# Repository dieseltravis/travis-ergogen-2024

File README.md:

# Travis's Ergogen Keyboard 2024 #
Built with Ergogen v4. *Beta* quality!

## Project Details ##
* `/config.yaml` Ergogen layout
* `/package.json` yarn commands and metadata
* `/output/outlines/` generated 2d models
* `/output/cases/` generated 3d models
* `/output/pcbs/` generated PCB
* `/footprints/travis/` Custom parts' footprints
    * `/footprints/travis/travis.pretty/` KiCad footprints
* `/key/` generator for individual key footprint (key-module.js)
    * `/keytest/` test for individual key footprint
* `/datasheets/` PDFs for some of the parts used
* `/kle/` keyboard-layout-editor.com layouts
* `/firmware/` qmk firmware compiles, but needs to be tested!

## References ##
* Ergogen project: https://github.com/ergogen/ergogen/
    * https://ergogen.cache.works/
    * https://ergogen.xyz/
* FlatFootFox's Let's Design A Keyboard With Ergogen v4 https://flatfootfox.com/ergogen-introduction/
* Footprints:
    * ceoloide's Ergogen PCB footprints https://github.com/ceoloide/ergogen-footprints
    * infused-kim's Ergogen PCB footprints https://github.com/infused-kim/kb_ergogen_fp/
    * TildeWill's Ergogen PCB footprints https://github.com/TildeWill/ergogen_footprints
    * MvEerd https://github.com/MvEerd/ergogen/tree/mveerd/src/footprints
    * daprice's keyswitches.pretty https://github.com/daprice/keyswitches.pretty
    * joe-scotto's scottokeebs: https://github.com/joe-scotto/scottokeebs/tree/main/Extras/ScottoKicad
    * Convert Kicad Footprints to Ergogen https://nilnil.notion.site/Convert-Kicad-Footprints-to-Ergogen-8340ce87ad554c69af4e3f92bc9a0898
    * KiCad Footprints: https://kicad.github.io/footprints/
* Other helpful build guides:
    * ceoloide's corney-island build https://github.com/ceoloide/corney-island
    * zzeneg's stront40 https://github.com/zzeneg/stront/tree/stront40
    * Minecatr's Splinar+ https://github.com/Minecatr/keyboards/
    * Kimiko Build Guide https://keycapsss.com/help/kimiko/buildguide_en
    * Nullbits Nibble https://github.com/nullbitsco/docs/blob/main/nibble/build_guide_en.md
    * Lagom https://github.com/mohoyt/lagom/
    * Sundown-keyboard https://github.com/Richiban/Sundown-keyboard/
    * Mantis hex ergo keyboard https://github.com/fxkuehl/mantis/
    * Sofle Keyboard https://github.com/josefadamcik/SofleKeyboard

## Parts ##

Aliexpress:
* Diodes: DO-35 1N4148 100pcs https://www.aliexpress.us/item/3256805608834808.html
* Rotary encoder: EC11 12.5mm 5pcs https://www.aliexpress.us/item/2251832789732148.html
* EVQWGD001 Encoder: https://www.aliexpress.us/item/3256806010310254.html
* IC SN74HC138N 10pcs https://www.aliexpress.us/item/3256806021872320.html
* RGB LEDs: SK6812 MINI-E 100pcs https://www.aliexpress.us/item/2255800289371100.html
* Capacitors: 104(0.1uF) 100pcs https://www.aliexpress.us/item/3256802104127109.html
* Resistor: 470R 100pcs https://www.aliexpress.us/item/3256801441680644.html
* Electrolytic Capacitor: 6.3V1000UF 6x11mm 10pcs https://www.aliexpress.us/item/3256802796040934.html

Adafruit:
* Adafruit KB2040 - RP2040 Kee Boar Driver https://www.adafruit.com/product/5302
* 5 @ Kailh Switch Sockets for MX-compatible Mechanical Keys - 20 Pack https://www.adafruit.com/product/4958
* 10 @ Kailh Mechanical Key Switches - Tactile Brown - 10 pack - Cherry MX Brown Compatible https://www.adafruit.com/product/4954
* 10 @ DSA Keycaps for MX Compatible Switches - 10 pack https://www.adafruit.com/product/5008
* USB A to USB C Cable - 2 meters long https://www.adafruit.com/product/5044

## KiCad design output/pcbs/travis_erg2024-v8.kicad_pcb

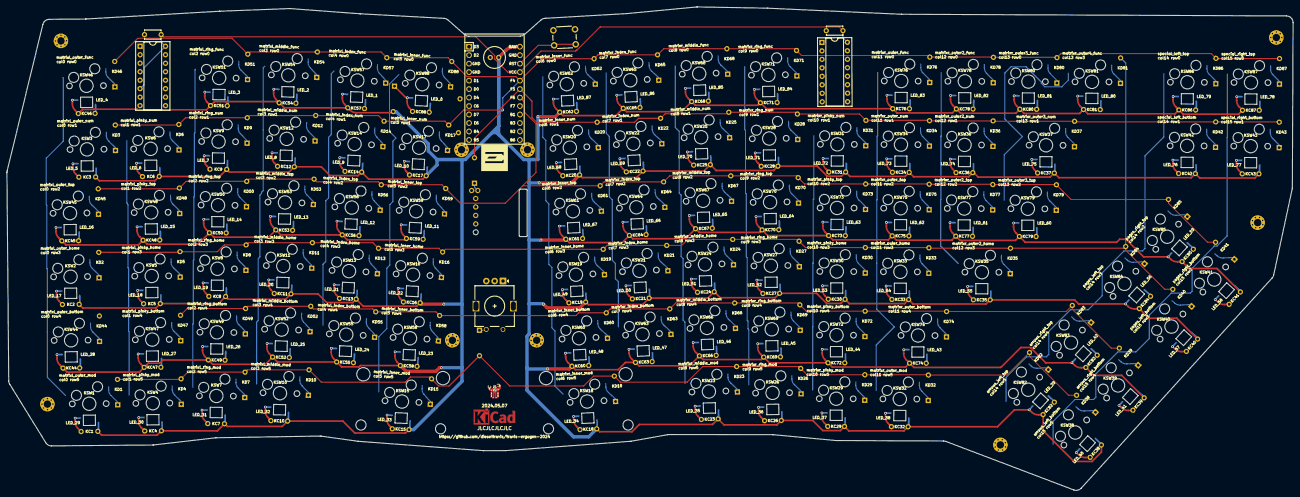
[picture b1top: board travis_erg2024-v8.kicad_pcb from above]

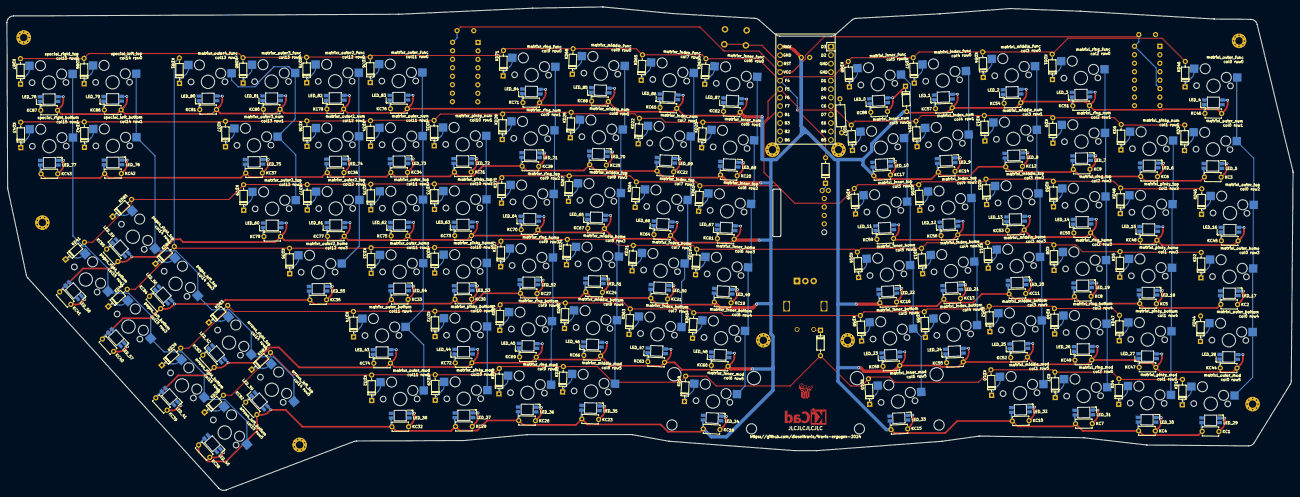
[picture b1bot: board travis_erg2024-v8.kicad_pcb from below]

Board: 2 copper layers, 385.3 x 144.8 mm, 379 parts (268 on the bottom side), 214 nets.

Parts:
C1: 6.3V 1000uF; C_Radial_D6.3mm_H11.0mm_P2.50mm
C2, C3: 104; C_Disc_D4.7mm_W2.5mm_P5.00mm
D1, D2, D3: 1N4148; Diode_DO-35
DIP1, DIP2: SN74HC138N; DIP-16_W7.62mm_Socket
HOLE1, HOLE2, HOLE3, HOLE4, HOLE5, HOLE6, HOLE7, HOLE8, HOLE9: MountingHole_2.2mm_M2_Pad_Via
KC1, KC2, KC3, KC4, KC5, KC6, KC7, KC8, KC9, KC10, KC11, KC12, KC13, KC14, KC15, KC16, KC17, KC18, KC19, KC20, KC21, KC22, KC23, KC24, KC25, KC26, KC27, KC28, KC29, KC30, KC31, KC32, KC33, KC34, KC35, KC36, KC37, KC38, KC39, KC40, KC41, KC42, KC43, KC44, KC45, KC46, KC47, KC48, KC49, KC50, KC51, KC52, KC53, KC54, KC55, KC56, KC57, KC58, KC59, KC60, KC61, KC62, KC63, KC64, KC65, KC66, KC67, KC68, KC69, KC70, KC71, KC72, KC73, KC74, KC75, KC76, KC77, KC78, KC79, KC80, KC81, KC82, KC83, KC84, KC85, KC86, KC87, KC88: 104; C_Disc_D4.7mm_W2.5mm_P5.00mm
KD1, KD2, KD3, KD4, KD5, KD6, KD7, KD8, KD9, KD10, KD11, KD12, KD13, KD14, KD15, KD16, KD17, KD18, KD19, KD20, KD21, KD22, KD23, KD24, KD25, KD26, KD27, KD28, KD29, KD30, KD31, KD32, KD33, KD34, KD35, KD36, KD37, KD38, KD39, KD40, KD41, KD42, KD43, KD44, KD45, KD46, KD47, KD48, KD49, KD50, KD51, KD52, KD53, KD54, KD55, KD56, KD57, KD58, KD59, KD60, KD61, KD62, KD63, KD64, KD65, KD66, KD67, KD68, KD69, KD70, KD71, KD72, KD73, KD74, KD75, KD76, KD77, KD78, KD79, KD80, KD81, KD82, KD83, KD84, KD85, KD86, KD87, KD88: 1N4148; Diode_DO-35
KSW1, KSW2, KSW3, KSW4, KSW5, KSW6, KSW7, KSW8, KSW9, KSW10, KSW11, KSW12, KSW13, KSW14, KSW15, KSW16, KSW17, KSW18, KSW19, KSW20, KSW21, KSW22, KSW23, KSW24, KSW25, KSW26, KSW27, KSW28, KSW29, KSW30, KSW31, KSW32, KSW33, KSW34, KSW35, KSW36, KSW37, KSW38, KSW39, KSW40, KSW41, KSW42, KSW43, KSW44, KSW45, KSW46, KSW47, KSW48, KSW49, KSW50, KSW51, KSW52, KSW53, KSW54, KSW55, KSW56, KSW57, KSW58, KSW59, KSW60, KSW61, KSW62, KSW63, KSW64, KSW65, KSW66, KSW67, KSW68, KSW69, KSW70, KSW71, KSW72, KSW73, KSW74, KSW75, KSW76, KSW77, KSW78, KSW79, KSW80, KSW81, KSW82, KSW83, KSW84, KSW85, KSW86, KSW87, KSW88: Kailh MX Switch Sockets; MX
LED_0-row0-col5, LED_1-row0-col4, LED_2-row0-col3, LED_3-row0-col2, LED_4-row0-col0, LED_5-row1-col0, LED_6-row1-col1, LED_7-row1-col2, LED_8-row1-col3, LED_9-row1-col4, LED_10-row1-col5, LED_11-row2-col5, LED_12-row2-col4, LED_13-row2-col3, LED_14-row2-col2, LED_15-row2-col1, LED_16-row2-col0, LED_17-row3-col0, LED_18-row3-col1, LED_19-row3-col2, LED_20-row3-col3, LED_21-row3-col4, LED_22-row3-col5, LED_23-row4-col5, LED_24-row4-col4, LED_25-row4-col3, LED_26-row4-col2, LED_27-row4-col1, LED_28-row4-col0, LED_29-row5-col0, LED_30-row5-col1, LED_31-row5-col2, LED_32-row5-col3, LED_33-row5-col5, LED_34-row5-col6, LED_35-row5-col8, LED_36-row5-col9, LED_37-row5-col10, LED_38-row5-col11, LED_39-row5-col14, LED_40-row5-col15, LED_41-row4-col15, LED_42-row4-col14, LED_43-row4-col11, LED_44-row4-col10, LED_45-row4-col9, LED_46-row4-col8, LED_47-row4-col7, LED_48-row4-col6, LED_49-row3-col6, LED_50-row3-col7, LED_51-row3-col8, LED_52-row3-col9, LED_53-row3-col10, LED_54-row3-col11, LED_55-row3-col12, LED_56-row3-col14, LED_57-row3-col15, LED_58-row2-col15, LED_59-row2-col14, LED_60-row2-col13, LED_61-row2-col12, LED_62-row2-col11, LED_63-row2-col10, LED_64-row2-col9, LED_65-row2-col8, LED_66-row2-col7, LED_67-row2-col6, LED_68-row1-col6, LED_69-row1-col7, LED_70-row1-col8, LED_71-row1-col9, LED_72-row1-col10, LED_73-row1-col11, LED_74-row1-col12, LED_75-row1-col13, LED_76-row1-col14, LED_77-row1-col15, LED_78-row0-col15, LED_79-row0-col14, LED_80-row3-col13, LED_81-row0-col13, LED_82-row0-col12, LED_83-row0-col11, LED_84-row0-col9, LED_85-row0-col8, LED_86-row0-col7, LED_87-row0-col6: SK6812mini-e; led_SK6812mini-e
LOGO1: ergogen_logo
LOGO2: travis
MCU1: Arduino Pro Micro; Arduino_Pro_Micro
R1: 470R; R_Axial_DIN0207_L6.3mm_D2.5mm_P10.16mm_Horizontal
ROT1: EC11; ec11
SCR1: EVQWGD001; evqwgd001
STAB2u1, STAB2u2: Stabilizer_MX_2.00u
SW1: 6mm button; SW_PUSH_6mm_H4.3mm
SYM1: KiCad-Logo_5mm_Copper

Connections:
GND: C1.2, C2.2, C3.2, DIP1.4, DIP1.8, DIP2.4, DIP2.5, DIP2.8, KC1.2, KC2.2, KC3.2, KC4.2, KC5.2, KC6.2, KC7.2, KC8.2, KC9.2, KC10.2, KC11.2, KC12.2, KC13.2, KC14.2, KC15.2, KC16.2, KC17.2, KC18.2, KC19.2, KC20.2, KC21.2, KC22.2, KC23.2, KC24.2, KC25.2, KC26.2, KC27.2, KC28.2, KC29.2, KC30.2, KC31.2, KC32.2, KC33.2, KC34.2, KC35.2, KC36.2, KC37.2, KC38.2, KC39.2, KC40.2, KC41.2, KC42.2, KC43.2, KC44.2, KC45.2, KC46.2, KC47.2, KC48.2, KC49.2, KC50.2, KC51.2, KC52.2, KC53.2, KC54.2, KC55.2, KC56.2, KC57.2, KC58.2, KC59.2, KC60.2, KC61.2, KC62.2, KC63.2, KC64.2, KC65.2, KC66.2, KC67.2, KC68.2, KC69.2, KC70.2, KC71.2, KC72.2, KC73.2, KC74.2, KC75.2, KC76.2, KC77.2, KC78.2, KC79.2, KC80.2, KC81.2, KC82.2, KC83.2, KC84.2, KC85.2, KC86.2, KC87.2, KC88.2, LED_0-row0-col5.3, LED_1-row0-col4.3, LED_2-row0-col3.3, LED_3-row0-col2.3, LED_4-row0-col0.3, LED_5-row1-col0.3, LED_6-row1-col1.3, LED_7-row1-col2.3, LED_8-row1-col3.3, LED_9-row1-col4.3, LED_10-row1-col5.3, LED_11-row2-col5.3, LED_12-row2-col4.3, LED_13-row2-col3.3, LED_14-row2-col2.3, LED_15-row2-col1.3, LED_16-row2-col0.3, LED_17-row3-col0.3, LED_18-row3-col1.3, LED_19-row3-col2.3, LED_20-row3-col3.3, LED_21-row3-col4.3, LED_22-row3-col5.3, LED_23-row4-col5.3, LED_24-row4-col4.3, LED_25-row4-col3.3, LED_26-row4-col2.3, LED_27-row4-col1.3, LED_28-row4-col0.3, LED_29-row5-col0.3, LED_30-row5-col1.3, LED_31-row5-col2.3, LED_32-row5-col3.3, LED_33-row5-col5.3, LED_34-row5-col6.3, LED_35-row5-col8.3, LED_36-row5-col9.3, LED_37-row5-col10.3, LED_38-row5-col11.3, LED_39-row5-col14.3, LED_40-row5-col15.3, LED_41-row4-col15.3, LED_42-row4-col14.3, LED_43-row4-col11.3, LED_44-row4-col10.3, LED_45-row4-col9.3, LED_46-row4-col8.3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
LED: MCU1.12, R1.1
LED_0: LED_0-row0-col5.4, R1.2
LED_1: LED_0-row0-col5.2, LED_1-row0-col4.4
LED_2: LED_1-row0-col4.2, LED_2-row0-col3.4
LED_3: LED_2-row0-col3.2, LED_3-row0-col2.4
LED_4: LED_3-row0-col2.2, LED_4-row0-col0.4
LED_5: LED_4-row0-col0.2, LED_5-row1-col0.4
LED_6: LED_5-row1-col0.2, LED_6-row1-col1.4
LED_7: LED_6-row1-col1.2, LED_7-row1-col2.4
LED_8: LED_7-row1-col2.2, LED_8-row1-col3.4
LED_9: LED_8-row1-col3.2, LED_9-row1-col4.4
LED_10: LED_9-row1-col4.2, LED_10-row1-col5.4
LED_11: LED_10-row1-col5.2, LED_11-row2-col5.4
LED_12: LED_11-row2-col5.2, LED_12-row2-col4.4
LED_13: LED_12-row2-col4.2, LED_13-row2-col3.4
LED_14: LED_13-row2-col3.2, LED_14-row2-col2.4
LED_15: LED_14-row2-col2.2, LED_15-row2-col1.4
LED_16: LED_15-row2-col1.2, LED_16-row2-col0.4
LED_17: LED_16-row2-col0.2, LED_17-row3-col0.4
LED_18: LED_17-row3-col0.2, LED_18-row3-col1.4
LED_19: LED_18-row3-col1.2, LED_19-row3-col2.4
LED_20: LED_19-row3-col2.2, LED_20-row3-col3.4
LED_21: LED_20-row3-col3.2, LED_21-row3-col4.4
LED_22: LED_21-row3-col4.2, LED_22-row3-col5.4
LED_23: LED_22-row3-col5.2, LED_23-row4-col5.4
LED_24: LED_23-row4-col5.2, LED_24-row4-col4.4
LED_25: LED_24-row4-col4.2, LED_25-row4-col3.4
LED_26: LED_25-row4-col3.2, LED_26-row4-col2.4
LED_27: LED_26-row4-col2.2, LED_27-row4-col1.4
LED_28: LED_27-row4-col1.2, LED_28-row4-col0.4
LED_29: LED_28-row4-col0.2, LED_29-row5-col0.4
LED_30: LED_29-row5-col0.2, LED_30-row5-col1.4
LED_31: LED_30-row5-col1.2, LED_31-row5-col2.4
LED_32: LED_31-row5-col2.2, LED_32-row5-col3.4
LED_33: LED_32-row5-col3.2, LED_33-row5-col5.4
LED_34: LED_33-row5-col5.2, LED_34-row5-col6.4
LED_35: LED_34-row5-col6.2, LED_35-row5-col8.4
LED_36: LED_35-row5-col8.2, LED_36-row5-col9.4
LED_37: LED_36-row5-col9.2, LED_37-row5-col10.4
LED_38: LED_37-row5-col10.2, LED_38-row5-col11.4
LED_39: LED_38-row5-col11.2, LED_39-row5-col14.4
LED_40: LED_39-row5-col14.2, LED_40-row5-col15.4
LED_41: LED_40-row5-col15.2, LED_41-row4-col15.4
LED_42: LED_41-row4-col15.2, LED_42-row4-col14.4
LED_43: LED_42-row4-col14.2, LED_43-row4-col11.4
LED_44: LED_43-row4-col11.2, LED_44-row4-col10.4
LED_45: LED_44-row4-col10.2, LED_45-row4-col9.4
LED_46: LED_45-row4-col9.2, LED_46-row4-col8.4
LED_47: LED_46-row4-col8.2, LED_47-row4-col7.4
LED_48: LED_47-row4-col7.2, LED_48-row4-col6.4
LED_49: LED_48-row4-col6.2, LED_49-row3-col6.4
LED_50: LED_49-row3-col6.2, LED_50-row3-col7.4
LED_51: LED_50-row3-col7.2, LED_51-row3-col8.4
LED_52: LED_51-row3-col8.2, LED_52-row3-col9.4
LED_53: LED_52-row3-col9.2, LED_53-row3-col10.4
LED_54: LED_53-row3-col10.2, LED_54-row3-col11.4
LED_55: LED_54-row3-col11.2, LED_55-row3-col12.4
LED_56: LED_55-row3-col12.2, LED_56-row3-col14.4
LED_57: LED_56-row3-col14.2, LED_57-row3-col15.4
LED_58: LED_57-row3-col15.2, LED_58-row2-col15.4
LED_59: LED_58-row2-col15.2, LED_59-row2-col14.4
LED_60: LED_59-row2-col14.2, LED_60-row2-col13.4
LED_61: LED_60-row2-col13.2, LED_61-row2-col12.4
LED_62: LED_61-row2-col12.2, LED_62-row2-col11.4
LED_63: LED_62-row2-col11.2, LED_63-row2-col10.4
LED_64: LED_63-row2-col10.2, LED_64-row2-col9.4
LED_65: LED_64-row2-col9.2, LED_65-row2-col8.4
LED_66: LED_65-row2-col8.2, LED_66-row2-col7.4
LED_67: LED_66-row2-col7.2, LED_67-row2-col6.4
LED_68: LED_67-row2-col6.2, LED_68-row1-col6.4
LED_69: LED_68-row1-col6.2, LED_69-row1-col7.4
LED_70: LED_69-row1-col7.2, LED_70-row1-col8.4
LED_71: LED_70-row1-col8.2, LED_71-row1-col9.4
LED_72: LED_71-row1-col9.2, LED_72-row1-col10.4
LED_73: LED_72-row1-col10.2, LED_73-row1-col11.4
LED_74: LED_73-row1-col11.2, LED_74-row1-col12.4
LED_75: LED_74-row1-col12.2, LED_75-row1-col13.4
LED_76: LED_75-row1-col13.2, LED_76-row1-col14.4
LED_77: LED_76-row1-col14.2, LED_77-row1-col15.4
LED_78: LED_77-row1-col15.2, LED_78-row0-col15.4
LED_79: LED_78-row0-col15.2, LED_79-row0-col14.4
LED_80: LED_79-row0-col14.2, LED_80-row3-col13.4
LED_81: LED_80-row3-col13.2, LED_81-row0-col13.4
LED_82: LED_81-row0-col13.2, LED_82-row0-col12.4
LED_83: LED_82-row0-col12.2, LED_83-row0-col11.4
LED_84: LED_83-row0-col11.2, LED_84-row0-col9.4
LED_85: LED_84-row0-col9.2, LED_85-row0-col8.4
LED_86: LED_85-row0-col8.2, LED_86-row0-col7.4
LED_87: LED_86-row0-col7.2, LED_87-row0-col6.4
RAW: C1.1, D1.2, KC1.1, KC2.1, KC3.1, KC4.1, KC5.1, KC6.1, KC7.1, KC8.1, KC9.1, KC10.1, KC11.1, KC12.1, KC13.1, KC14.1, KC15.1, KC16.1, KC17.1, KC18.1, KC19.1, KC20.1, KC21.1, KC22.1, KC23.1, KC24.1, KC25.1, KC26.1, KC27.1, KC28.1, KC29.1, KC30.1, KC31.1, KC32.1, KC33.1, KC34.1, KC35.1, KC36.1, KC37.1, KC38.1, KC39.1, KC40.1, KC41.1, KC42.1, KC43.1, KC44.1, KC45.1, KC46.1, KC47.1, KC48.1, KC49.1, KC50.1, KC51.1, KC52.1, KC53.1, KC54.1, KC55.1, KC56.1, KC57.1, KC58.1, KC59.1, KC60.1, KC61.1, KC62.1, KC63.1, KC64.1, KC65.1, KC66.1, KC67.1, KC68.1, KC69.1, KC70.1, KC71.1, KC72.1, KC73.1, KC74.1, KC75.1, KC76.1, KC77.1, KC78.1, KC79.1, KC80.1, KC81.1, KC82.1, KC83.1, KC84.1, KC85.1, KC86.1, KC87.1, LED_1-row0-col4.1, LED_2-row0-col3.1, LED_3-row0-col2.1, LED_4-row0-col0.1, LED_5-row1-col0.1, LED_6-row1-col1.1, LED_7-row1-col2.1, LED_8-row1-col3.1, LED_9-row1-col4.1, LED_10-row1-col5.1, LED_11-row2-col5.1, LED_12-row2-col4.1, LED_13-row2-col3.1, LED_14-row2-col2.1, LED_15-row2-col1.1, LED_16-row2-col0.1, LED_17-row3-col0.1, LED_18-row3-col1.1, LED_19-row3-col2.1, LED_20-row3-col3.1, LED_21-row3-col4.1, LED_22-row3-col5.1, LED_23-row4-col5.1, LED_24-row4-col4.1, LED_25-row4-col3.1, LED_26-row4-col2.1, LED_27-row4-col1.1, LED_28-row4-col0.1, LED_29-row5-col0.1, LED_30-row5-col1.1, LED_31-row5-col2.1, LED_32-row5-col3.1, LED_33-row5-col5.1, LED_34-row5-col6.1, LED_35-row5-col8.1, LED_36-row5-col9.1, LED_37-row5-col10.1, LED_38-row5-col11.1, LED_39-row5-col14.1, LED_40-row5-col15.1, LED_41-row4-col15.1, LED_42-row4-col14.1, LED_43-row4-col11.1, LED_44-row4-col10.1, LED_45-row4-col9.1, LED_46-row4-col8.1, LED_47-row4-col7.1, LED_48-row4-col6.1, LED_49-row3-col6.1, LED_50-row3-col7.1, LED_51-row3-col8.1, LED_52-row3-col9.1, LED_53-row3-col10.1, LED_54-row3-col11.1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
RAWD: D1.1, KC88.1, LED_0-row0-col5.1
RST: MCU1.22, SW1.2
VCC: C2.1, C3.1, DIP1.6, DIP1.16, DIP2.16, MCU1.21
arrows_left_bottom: KD38.1, KSW38.2
arrows_left_top: KD82.1, KSW82.2
arrows_right_bottom: KD39.1, KSW39.2
arrows_right_top: KD83.1, KSW83.2
col0: DIP1.15, KSW1.1, KSW2.1, KSW3.1, KSW44.1, KSW45.1, KSW46.1
col1: DIP1.14, KSW4.1, KSW5.1, KSW6.1, KSW47.1, KSW48.1, SCR1.S1
col2: DIP1.13, KSW7.1, KSW8.1, KSW9.1, KSW49.1, KSW50.1, KSW51.1
col3: DIP1.12, KSW10.1, KSW11.1, KSW12.1, KSW52.1, KSW53.1, KSW54.1
col4: DIP1.11, KSW13.1, KSW14.1, KSW55.1, KSW56.1, KSW57.1, ROT1.1
col5: DIP1.10, KSW15.1, KSW16.1, KSW17.1, KSW58.1, KSW59.1, KSW88.1
col6: DIP1.9, KSW18.1, KSW19.1, KSW20.1, KSW60.1, KSW61.1, KSW62.1
col7: DIP1.7, KSW21.1, KSW22.1, KSW63.1, KSW64.1, KSW65.1
col8: DIP2.15, KSW23.1, KSW24.1, KSW25.1, KSW66.1, KSW67.1, KSW68.1
col9: DIP2.14, KSW26.1, KSW27.1, KSW28.1, KSW69.1, KSW70.1, KSW71.1
col10: DIP2.13, KSW29.1, KSW30.1, KSW31.1, KSW72.1, KSW73.1
col11: DIP2.12, KSW32.1, KSW33.1, KSW34.1, KSW74.1, KSW75.1, KSW76.1
col12: DIP2.11, KSW35.1, KSW36.1, KSW77.1, KSW78.1
col13: DIP2.10, KSW37.1, KSW79.1, KSW80.1, KSW81.1
col14: DIP2.9, KSW42.1, KSW82.1, KSW83.1, KSW84.1, KSW85.1, KSW86.1
col15: DIP2.7, KSW38.1, KSW39.1, KSW40.1, KSW41.1, KSW43.1, KSW87.1
encA: MCU1.14, ROT1.A
encC: MCU1.13, ROT1.C
enc_to: D3.1, ROT1.2
matrixl_index_bottom: KD55.1, KSW55.2
matrixl_index_func: KD57.1, KSW57.2
matrixl_index_home: KD13.1, KSW13.2
matrixl_index_num: KD14.1, KSW14.2
matrixl_index_top: KD56.1, KSW56.2
matrixl_inner_bottom: KD58.1, KSW58.2
matrixl_inner_func: KD88.1, KSW88.2
matrixl_inner_home: KD16.1, KSW16.2
matrixl_inner_mod: KD15.1, KSW15.2
matrixl_inner_num: KD17.1, KSW17.2
matrixl_inner_top: KD59.1, KSW59.2
matrixl_middle_bottom: KD52.1, KSW52.2
matrixl_middle_func: KD54.1, KSW54.2
matrixl_middle_home: KD11.1, KSW11.2
matrixl_middle_mod: KD10.1, KSW10.2
matrixl_middle_num: KD12.1, KSW12.2
matrixl_middle_top: KD53.1, KSW53.2
matrixl_outer_bottom: KD44.1, KSW44.2
matrixl_outer_func: KD46.1, KSW46.2
matrixl_outer_home: KD2.1, KSW2.2
matrixl_outer_mod: KD1.1, KSW1.2
matrixl_outer_num: KD3.1, KSW3.2
matrixl_outer_top: KD45.1, KSW45.2
matrixl_pinky_bottom: KD47.1, KSW47.2
matrixl_pinky_home: KD5.1, KSW5.2
matrixl_pinky_mod: KD4.1, KSW4.2
matrixl_pinky_num: KD6.1, KSW6.2
matrixl_pinky_top: KD48.1, KSW48.2
matrixl_ring_bottom: KD49.1, KSW49.2
matrixl_ring_func: KD51.1, KSW51.2
matrixl_ring_home: KD8.1, KSW8.2
matrixl_ring_mod: KD7.1, KSW7.2
matrixl_ring_num: KD9.1, KSW9.2
matrixl_ring_top: KD50.1, KSW50.2
matrixr_index_bottom: KD63.1, KSW63.2
matrixr_index_func: KD65.1, KSW65.2
matrixr_index_home: KD21.1, KSW21.2
matrixr_index_num: KD22.1, KSW22.2
matrixr_index_top: KD64.1, KSW64.2
matrixr_inner_bottom: KD60.1, KSW60.2
matrixr_inner_func: KD62.1, KSW62.2
matrixr_inner_home: KD19.1, KSW19.2
matrixr_inner_mod: KD18.1, KSW18.2
matrixr_inner_num: KD20.1, KSW20.2
matrixr_inner_top: KD61.1, KSW61.2
matrixr_middle_bottom: KD66.1, KSW66.2
matrixr_middle_func: KD68.1, KSW68.2
matrixr_middle_home: KD24.1, KSW24.2
matrixr_middle_mod: KD23.1, KSW23.2
matrixr_middle_num: KD25.1, KSW25.2
matrixr_middle_top: KD67.1, KSW67.2
matrixr_outer2_func: KD78.1, KSW78.2
matrixr_outer2_home: KD35.1, KSW35.2
matrixr_outer2_num: KD36.1, KSW36.2
matrixr_outer2_top: KD77.1, KSW77.2
matrixr_outer3_func: KD80.1, KSW80.2
matrixr_outer3_num: KD37.1, KSW37.2
matrixr_outer3_top: KD79.1, KSW79.2
matrixr_outer4_func: KD81.1, KSW81.2
matrixr_outer_bottom: KD74.1, KSW74.2
matrixr_outer_func: KD76.1, KSW76.2
matrixr_outer_home: KD33.1, KSW33.2
matrixr_outer_mod: KD32.1, KSW32.2
matrixr_outer_num: KD34.1, KSW34.2
matrixr_outer_top: KD75.1, KSW75.2
matrixr_pinky_bottom: KD72.1, KSW72.2
matrixr_pinky_home: KD30.1, KSW30.2
matrixr_pinky_mod: KD29.1, KSW29.2
matrixr_pinky_num: KD31.1, KSW31.2
matrixr_pinky_top: KD73.1, KSW73.2
matrixr_ring_bottom: KD69.1, KSW69.2
matrixr_ring_func: KD71.1, KSW71.2
matrixr_ring_home: KD27.1, KSW27.2
matrixr_ring_mod: KD26.1, KSW26.2
matrixr_ring_num: KD28.1, KSW28.2
matrixr_ring_top: KD70.1, KSW70.2
mux0: DIP1.1, DIP2.1, MCU1.8
mux1: DIP1.2, DIP2.2, MCU1.7
mux2: DIP1.3, DIP2.3, MCU1.6
mux3: DIP1.5, DIP2.6, MCU1.5
pages_left_bottom: KD40.1, KSW40.2
pages_left_top: KD84.1, KSW84.2
pages_right_bottom: KD41.1, KSW41.2
pages_right_top: KD85.1, KSW85.2
row0: D2.2, KD46.2, KD51.2, KD54.2, KD57.2, KD62.2, KD65.2, KD68.2, KD71.2, KD76.2, KD78.2, KD80.2, KD86.2, KD87.2, KD88.2, MCU1.20
row1: KD3.2, KD6.2, KD9.2, KD12.2, KD14.2, KD17.2, KD20.2, KD22.2, KD25.2, KD28.2, KD31.2, KD34.2, KD36.2, KD37.2, KD42.2, KD43.2, MCU1.19
row2: KD41.2, KD45.2, KD48.2, KD50.2, KD53.2, KD56.2, KD59.2, KD61.2, KD64.2, KD67.2, KD70.2, KD73.2, KD75.2, KD77.2, KD79.2, KD85.2, MCU1.18
row3: KD2.2, KD5.2, KD8.2, KD11.2, KD13.2, KD16.2, KD19.2, KD21.2, KD24.2, KD27.2, KD30.2, KD33.2, KD35.2, KD40.2, KD81.2, KD84.2, MCU1.17
row4: KD39.2, KD44.2, KD47.2, KD49.2, KD52.2, KD55.2, KD58.2, KD60.2, KD63.2, KD66.2, KD69.2, KD72.2, KD74.2, KD83.2, MCU1.16
row5: D3.2, KD1.2, KD4.2, KD7.2, KD10.2, KD15.2, KD18.2, KD23.2, KD26.2, KD29.2, KD32.2, KD38.2, KD82.2, MCU1.15
scrA: MCU1.10, SCR1.A
scrC: MCU1.9, SCR1.C
scr_to: D2.1, SCR1.S2
special_left_bottom: KD42.1, KSW42.2
special_left_top: KD86.1, KSW86.2
special_right_bottom: KD43.1, KSW43.2
special_right_top: KD87.1, KSW87.2

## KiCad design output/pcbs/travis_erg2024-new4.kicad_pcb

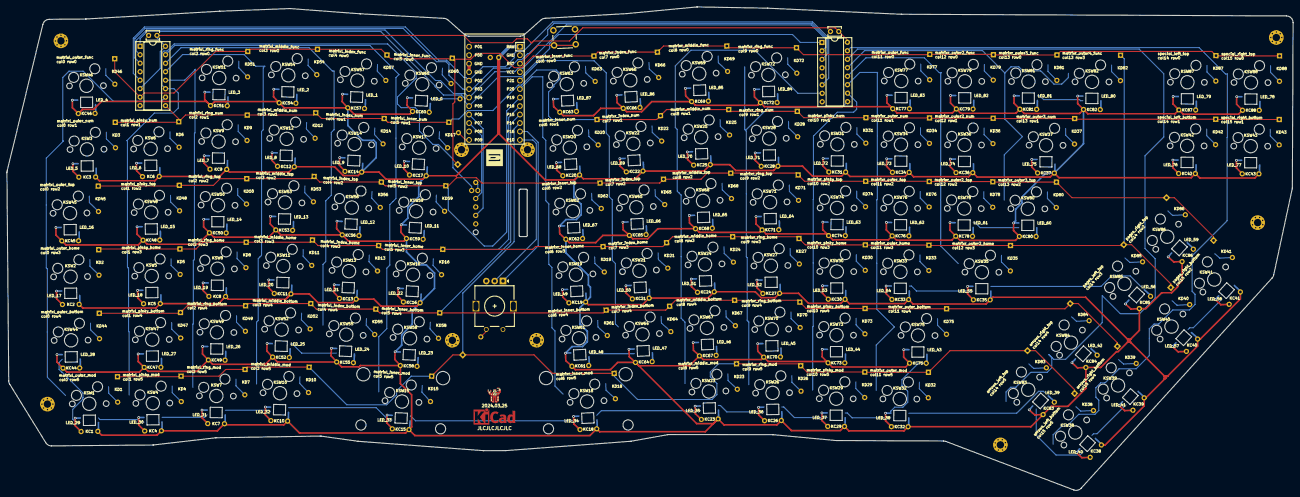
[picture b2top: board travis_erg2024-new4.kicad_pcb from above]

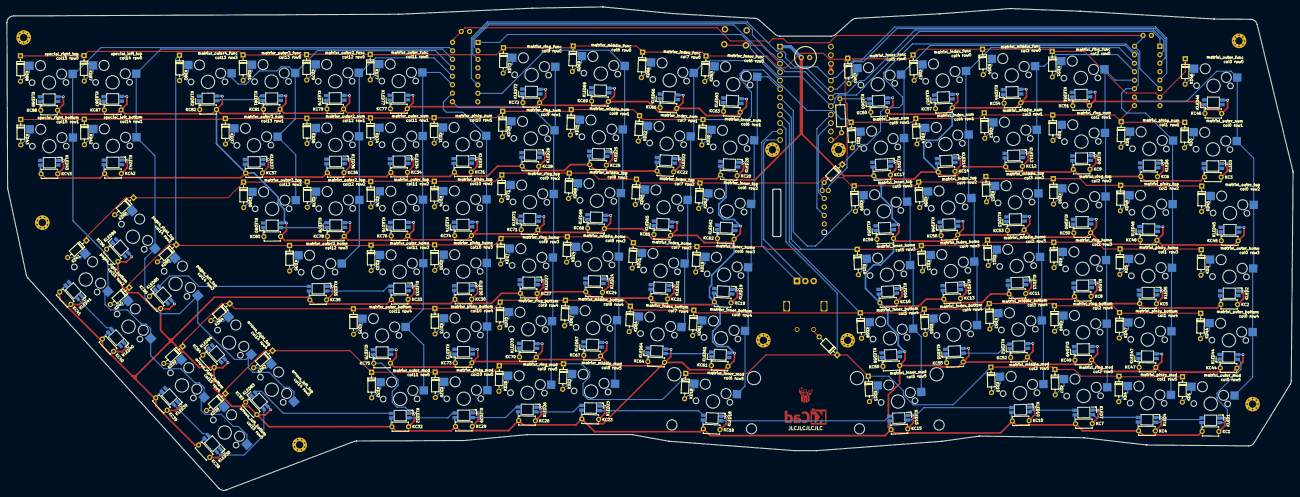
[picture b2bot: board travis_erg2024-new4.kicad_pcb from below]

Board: 2 copper layers, 385.3 x 144.8 mm, 377 parts (268 on the bottom side), 210 nets.

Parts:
C1: C_Radial_D6.3mm_H11.0mm_P2.50mm
C2, C3: C_Disc_D3.8mm_W2.6mm_P2.50mm
D1, D2: 1N4148; Diode_DO-35
DIP1, DIP2: DIP-16_W7.62mm_Socket
HOLE1, HOLE2, HOLE3, HOLE4, HOLE5, HOLE6, HOLE7, HOLE8, HOLE9: MountingHole_2.2mm_M2_Pad_Via
KC1, KC2, KC3, KC4, KC5, KC6, KC7, KC8, KC9, KC10, KC11, KC12, KC13, KC14, KC15, KC16, KC17, KC18, KC19, KC20, KC21, KC22, KC23, KC24, KC25, KC26, KC27, KC28, KC29, KC30, KC31, KC32, KC33, KC34, KC35, KC36, KC37, KC38, KC39, KC40, KC41, KC42, KC43, KC44, KC45, KC46, KC47, KC48, KC49, KC50, KC51, KC52, KC53, KC54, KC55, KC56, KC57, KC58, KC59, KC60, KC61, KC62, KC63, KC64, KC65, KC66, KC67, KC68, KC69, KC70, KC71, KC72, KC73, KC74, KC75, KC76, KC77, KC78, KC79, KC80, KC81, KC82, KC83, KC84, KC85, KC86, KC87, KC88: 104; C_Disc_D4.7mm_W2.5mm_P5.00mm
KD1, KD2, KD3, KD4, KD5, KD6, KD7, KD8, KD9, KD10, KD11, KD12, KD13, KD14, KD15, KD16, KD17, KD18, KD19, KD20, KD21, KD22, KD23, KD24, KD25, KD26, KD27, KD28, KD29, KD30, KD31, KD32, KD33, KD34, KD35, KD36, KD37, KD38, KD39, KD40, KD41, KD42, KD43, KD44, KD45, KD46, KD47, KD48, KD49, KD50, KD51, KD52, KD53, KD54, KD55, KD56, KD57, KD58, KD59, KD60, KD61, KD62, KD63, KD64, KD65, KD66, KD67, KD68, KD69, KD70, KD71, KD72, KD73, KD74, KD75, KD76, KD77, KD78, KD79, KD80, KD81, KD82, KD83, KD84, KD85, KD86, KD87, KD88: 1N4148; Diode_DO-35
KLED1, KLED2, KLED3, KLED4, KLED5, KLED6, KLED7, KLED8, KLED9, KLED10, KLED11, KLED12, KLED13, KLED14, KLED15, KLED16, KLED17, KLED18, KLED19, KLED20, KLED21, KLED22, KLED23, KLED24, KLED25, KLED26, KLED27, KLED28, KLED29, KLED30, KLED31, KLED32, KLED33, KLED34, KLED35, KLED36, KLED37, KLED38, KLED39, KLED40, KLED41, KLED42, KLED43, KLED44, KLED45, KLED46, KLED47, KLED48, KLED49, KLED50, KLED51, KLED52, KLED53, KLED54, KLED55, KLED56, KLED57, KLED58, KLED59, KLED60, KLED61, KLED62, KLED63, KLED64, KLED65, KLED66, KLED67, KLED68, KLED69, KLED70, KLED71, KLED72, KLED73, KLED74, KLED75, KLED76, KLED77, KLED78, KLED79, KLED80, KLED81, KLED82, KLED83, KLED84, KLED85, KLED86, KLED87, KLED88: SK6812mini-e; led_SK6812mini-e (per-key single-side)
KSW1, KSW2, KSW3, KSW4, KSW5, KSW6, KSW7, KSW8, KSW9, KSW10, KSW11, KSW12, KSW13, KSW14, KSW15, KSW16, KSW17, KSW18, KSW19, KSW20, KSW21, KSW22, KSW23, KSW24, KSW25, KSW26, KSW27, KSW28, KSW29, KSW30, KSW31, KSW32, KSW33, KSW34, KSW35, KSW36, KSW37, KSW38, KSW39, KSW40, KSW41, KSW42, KSW43, KSW44, KSW45, KSW46, KSW47, KSW48, KSW49, KSW50, KSW51, KSW52, KSW53, KSW54, KSW55, KSW56, KSW57, KSW58, KSW59, KSW60, KSW61, KSW62, KSW63, KSW64, KSW65, KSW66, KSW67, KSW68, KSW69, KSW70, KSW71, KSW72, KSW73, KSW74, KSW75, KSW76, KSW77, KSW78, KSW79, KSW80, KSW81, KSW82, KSW83, KSW84, KSW85, KSW86, KSW87, KSW88: Kailh MX Switch Sockets; MX
LOGO1: ergogen
LOGO2: travis
MCU1: ProMicro
R1: R_Axial_DIN0207_L6.3mm_D2.5mm_P10.16mm_Horizontal
ROT1: rotary_encoder
STAB2u1, STAB2u2: Stabilizer_MX_2.00u
SW1: SW_PUSH_6mm_H4.3mm
SYM1: KiCad-Logo_5mm_Copper

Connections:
GND: C1.2, C2.2, C3.2, DIP1.4, DIP1.8, DIP2.4, DIP2.5, DIP2.8, KC1.2, KC2.2, KC3.2, KC4.2, KC5.2, KC6.2, KC7.2, KC8.2, KC9.2, KC10.2, KC11.2, KC12.2, KC13.2, KC14.2, KC15.2, KC16.2, KC17.2, KC18.2, KC19.2, KC20.2, KC21.2, KC22.2, KC23.2, KC24.2, KC25.2, KC26.2, KC27.2, KC28.2, KC29.2, KC30.2, KC31.2, KC32.2, KC33.2, KC34.2, KC35.2, KC36.2, KC37.2, KC38.2, KC39.2, KC40.2, KC41.2, KC42.2, KC43.2, KC44.2, KC45.2, KC46.2, KC47.2, KC48.2, KC49.2, KC50.2, KC51.2, KC52.2, KC53.2, KC54.2, KC55.2, KC56.2, KC57.2, KC58.2, KC59.2, KC60.2, KC61.2, KC62.2, KC63.2, KC64.2, KC65.2, KC66.2, KC67.2, KC68.2, KC69.2, KC70.2, KC71.2, KC72.2, KC73.2, KC74.2, KC75.2, KC76.2, KC77.2, KC78.2, KC79.2, KC80.2, KC81.2, KC82.2, KC83.2, KC84.2, KC85.2, KC86.2, KC87.2, KC88.2, KLED1.3, KLED2.3, KLED3.3, KLED4.3, KLED5.3, KLED6.3, KLED7.3, KLED8.3, KLED9.3, KLED10.3, KLED11.3, KLED12.3, KLED13.3, KLED14.3, KLED15.3, KLED16.3, KLED17.3, KLED18.3, KLED19.3, KLED20.3, KLED21.3, KLED22.3, KLED23.3, KLED24.3, KLED25.3, KLED26.3, KLED27.3, KLED28.3, KLED29.3, KLED30.3, KLED31.3, KLED32.3, KLED33.3, KLED34.3, KLED35.3, KLED36.3, KLED37.3, KLED38.3, KLED39.3, KLED40.3, KLED41.3, KLED42.3, KLED43.3, KLED44.3, KLED45.3, KLED46.3, KLED47.3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
LED: MCU1.24, R1.1
LED_0: KLED60.4, R1.2
LED_1: KLED57.4, KLED60.2
LED_2: KLED54.4, KLED57.2
LED_3: KLED51.4, KLED54.2
LED_4: KLED46.4, KLED51.2
LED_5: KLED3.4, KLED46.2
LED_6: KLED3.2, KLED6.4
LED_7: KLED6.2, KLED9.4
LED_8: KLED9.2, KLED12.4
LED_9: KLED12.2, KLED14.4
LED_10: KLED14.2, KLED17.4
LED_11: KLED17.2, KLED59.4
LED_12: KLED56.4, KLED59.2
LED_13: KLED53.4, KLED56.2
LED_14: KLED50.4, KLED53.2
LED_15: KLED48.4, KLED50.2
LED_16: KLED45.4, KLED48.2
LED_17: KLED2.4, KLED45.2
LED_18: KLED2.2, KLED5.4
LED_19: KLED5.2, KLED8.4
LED_20: KLED8.2, KLED11.4
LED_21: KLED11.2, KLED13.4
LED_22: KLED13.2, KLED16.4
LED_23: KLED16.2, KLED58.4
LED_24: KLED55.4, KLED58.2
LED_25: KLED52.4, KLED55.2
LED_26: KLED49.4, KLED52.2
LED_27: KLED47.4, KLED49.2
LED_28: KLED44.4, KLED47.2
LED_29: KLED1.4, KLED44.2
LED_30: KLED1.2, KLED4.4
LED_31: KLED4.2, KLED7.4
LED_32: KLED7.2, KLED10.4
LED_33: KLED10.2, KLED15.4
LED_34: KLED15.2, KLED18.4
LED_35: KLED18.2, KLED23.4
LED_36: KLED23.2, KLED26.4
LED_37: KLED26.2, KLED29.4
LED_38: KLED29.2, KLED32.4
LED_39: KLED32.2, KLED83.4
LED_40: KLED38.4, KLED83.2
LED_41: KLED38.2, KLED39.4
LED_42: KLED39.2, KLED84.4
LED_43: KLED75.4, KLED84.2
LED_44: KLED73.4, KLED75.2
LED_45: KLED70.4, KLED73.2
LED_46: KLED67.4, KLED70.2
LED_47: KLED64.4, KLED67.2
LED_48: KLED61.4, KLED64.2
LED_49: KLED19.4, KLED61.2
LED_50: KLED19.2, KLED21.4
LED_51: KLED21.2, KLED24.4
LED_52: KLED24.2, KLED27.4
LED_53: KLED27.2, KLED30.4
LED_54: KLED30.2, KLED33.4
LED_55: KLED33.2, KLED35.4
LED_56: KLED35.2, KLED85.4
LED_57: KLED40.4, KLED85.2
LED_58: KLED40.2, KLED41.4
LED_59: KLED41.2, KLED86.4
LED_60: KLED80.4, KLED86.2
LED_61: KLED78.4, KLED80.2
LED_62: KLED76.4, KLED78.2
LED_63: KLED74.4, KLED76.2
LED_64: KLED71.4, KLED74.2
LED_65: KLED68.4, KLED71.2
LED_66: KLED65.4, KLED68.2
LED_67: KLED62.4, KLED65.2
LED_68: KLED20.4, KLED62.2
LED_69: KLED20.2, KLED22.4
LED_70: KLED22.2, KLED25.4
LED_71: KLED25.2, KLED28.4
LED_72: KLED28.2, KLED31.4
LED_73: KLED31.2, KLED34.4
LED_74: KLED34.2, KLED36.4
LED_75: KLED36.2, KLED37.4
LED_76: KLED37.2, KLED42.4
LED_77: KLED42.2, KLED43.4
LED_78: KLED43.2, KLED88.4
LED_79: KLED87.4, KLED88.2
LED_80: KLED82.4, KLED87.2
LED_81: KLED81.4, KLED82.2
LED_82: KLED79.4, KLED81.2
LED_83: KLED77.4, KLED79.2
LED_84: KLED72.4, KLED77.2
LED_85: KLED69.4, KLED72.2
LED_86: KLED66.4, KLED69.2
LED_87: KLED63.4, KLED66.2
RAW: C1.1, KC1.1, KC2.1, KC3.1, KC4.1, KC5.1, KC6.1, KC7.1, KC8.1, KC9.1, KC10.1, KC11.1, KC12.1, KC13.1, KC14.1, KC15.1, KC16.1, KC17.1, KC18.1, KC19.1, KC20.1, KC21.1, KC22.1, KC23.1, KC24.1, KC25.1, KC26.1, KC27.1, KC28.1, KC29.1, KC30.1, KC31.1, KC32.1, KC33.1, KC34.1, KC35.1, KC36.1, KC37.1, KC38.1, KC39.1, KC40.1, KC41.1, KC42.1, KC43.1, KC44.1, KC45.1, KC46.1, KC47.1, KC48.1, KC49.1, KC50.1, KC51.1, KC52.1, KC53.1, KC54.1, KC55.1, KC56.1, KC57.1, KC58.1, KC59.1, KC60.1, KC61.1, KC62.1, KC63.1, KC64.1, KC65.1, KC66.1, KC67.1, KC68.1, KC69.1, KC70.1, KC71.1, KC72.1, KC73.1, KC74.1, KC75.1, KC76.1, KC77.1, KC78.1, KC79.1, KC80.1, KC81.1, KC82.1, KC83.1, KC84.1, KC85.1, KC86.1, KC87.1, KC88.1, KLED1.1, KLED2.1, KLED3.1, KLED4.1, KLED5.1, KLED6.1, KLED7.1, KLED8.1, KLED9.1, KLED10.1, KLED11.1, KLED12.1, KLED13.1, KLED14.1, KLED15.1, KLED16.1, KLED17.1, KLED18.1, KLED19.1, KLED20.1, KLED21.1, KLED22.1, KLED23.1, KLED24.1, KLED25.1, KLED26.1, KLED27.1, KLED28.1, KLED29.1, KLED30.1, KLED31.1, KLED32.1, KLED33.1, KLED34.1, KLED35.1, KLED36.1, KLED37.1, KLED38.1, KLED39.1, KLED40.1, KLED41.1, KLED42.1, KLED43.1, KLED44.1, KLED45.1, KLED46.1, KLED47.1, KLED48.1, KLED49.1, KLED50.1, KLED51.1, KLED52.1, KLED53.1, KLED54.1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
RST: MCU1.3, SW1.2
VCC: C2.1, C3.1, DIP1.6, DIP1.16, DIP2.16, MCU1.4
arrows_left_bottom: KD38.2, KSW38.2
arrows_left_top: KD83.2, KSW83.2
arrows_right_bottom: KD39.2, KSW39.2
arrows_right_top: KD84.2, KSW84.2
col0: DIP1.10, KSW1.1, KSW2.1, KSW3.1, KSW44.1, KSW45.1, KSW46.1
col1: DIP1.11, KSW4.1, KSW5.1, KSW6.1, KSW47.1, KSW48.1
col2: DIP1.12, KSW7.1, KSW8.1, KSW9.1, KSW49.1, KSW50.1, KSW51.1
col3: DIP1.13, KSW10.1, KSW11.1, KSW12.1, KSW52.1, KSW53.1, KSW54.1
col4: DIP1.14, KSW13.1, KSW14.1, KSW55.1, KSW56.1, KSW57.1, ROT1.1
col5: DIP1.15, KSW15.1, KSW16.1, KSW17.1, KSW58.1, KSW59.1, KSW60.1
col6: KSW18.1, KSW19.1, KSW20.1, KSW61.1, KSW62.1, KSW63.1, MCU1.6
col7: KSW21.1, KSW22.1, KSW64.1, KSW65.1, KSW66.1, MCU1.5
col8: DIP2.7, KSW23.1, KSW24.1, KSW25.1, KSW67.1, KSW68.1, KSW69.1
col9: DIP2.9, KSW26.1, KSW27.1, KSW28.1, KSW70.1, KSW71.1, KSW72.1
col10: DIP2.10, KSW29.1, KSW30.1, KSW31.1, KSW73.1, KSW74.1
col11: DIP2.11, KSW32.1, KSW33.1, KSW34.1, KSW75.1, KSW76.1, KSW77.1
col12: DIP2.12, KSW35.1, KSW36.1, KSW78.1, KSW79.1
col13: DIP2.13, KSW37.1, KSW80.1, KSW81.1, KSW82.1
col14: DIP2.14, KSW42.1, KSW83.1, KSW84.1, KSW85.1, KSW86.1, KSW87.1
col15: DIP2.15, KSW38.1, KSW39.1, KSW40.1, KSW41.1, KSW43.1, KSW88.1
encA: MCU1.11, ROT1.A
encC: MCU1.12, ROT1.C
enc_to: D2.2, ROT1.2
matrixl_index_bottom: KD55.2, KSW55.2
matrixl_index_func: KD57.2, KSW57.2
matrixl_index_home: KD13.2, KSW13.2
matrixl_index_num: KD14.2, KSW14.2
matrixl_index_top: KD56.2, KSW56.2
matrixl_inner_bottom: KD58.2, KSW58.2
matrixl_inner_func: KD60.2, KSW60.2
matrixl_inner_home: KD16.2, KSW16.2
matrixl_inner_mod: KD15.2, KSW15.2
matrixl_inner_num: KD17.2, KSW17.2
matrixl_inner_top: KD59.2, KSW59.2
matrixl_middle_bottom: KD52.2, KSW52.2
matrixl_middle_func: KD54.2, KSW54.2
matrixl_middle_home: KD11.2, KSW11.2
matrixl_middle_mod: KD10.2, KSW10.2
matrixl_middle_num: KD12.2, KSW12.2
matrixl_middle_top: KD53.2, KSW53.2
matrixl_outer_bottom: KD44.2, KSW44.2
matrixl_outer_func: KD46.2, KSW46.2
matrixl_outer_home: KD2.2, KSW2.2
matrixl_outer_mod: KD1.2, KSW1.2
matrixl_outer_num: KD3.2, KSW3.2
matrixl_outer_top: KD45.2, KSW45.2
matrixl_pinky_bottom: KD47.2, KSW47.2
matrixl_pinky_home: KD5.2, KSW5.2
matrixl_pinky_mod: KD4.2, KSW4.2
matrixl_pinky_num: KD6.2, KSW6.2
matrixl_pinky_top: KD48.2, KSW48.2
matrixl_ring_bottom: KD49.2, KSW49.2
matrixl_ring_func: KD51.2, KSW51.2
matrixl_ring_home: KD8.2, KSW8.2
matrixl_ring_mod: KD7.2, KSW7.2
matrixl_ring_num: KD9.2, KSW9.2
matrixl_ring_top: KD50.2, KSW50.2
matrixr_index_bottom: KD64.2, KSW64.2
matrixr_index_func: KD66.2, KSW66.2
matrixr_index_home: KD21.2, KSW21.2
matrixr_index_num: KD22.2, KSW22.2
matrixr_index_top: KD65.2, KSW65.2
matrixr_inner_bottom: KD61.2, KSW61.2
matrixr_inner_func: KD63.2, KSW63.2
matrixr_inner_home: KD19.2, KSW19.2
matrixr_inner_mod: KD18.2, KSW18.2
matrixr_inner_num: KD20.2, KSW20.2
matrixr_inner_top: KD62.2, KSW62.2
matrixr_middle_bottom: KD67.2, KSW67.2
matrixr_middle_func: KD69.2, KSW69.2
matrixr_middle_home: KD24.2, KSW24.2
matrixr_middle_mod: KD23.2, KSW23.2
matrixr_middle_num: KD25.2, KSW25.2
matrixr_middle_top: KD68.2, KSW68.2
matrixr_outer2_func: KD79.2, KSW79.2
matrixr_outer2_home: KD35.2, KSW35.2
matrixr_outer2_num: KD36.2, KSW36.2
matrixr_outer2_top: KD78.2, KSW78.2
matrixr_outer3_func: KD81.2, KSW81.2
matrixr_outer3_num: KD37.2, KSW37.2
matrixr_outer3_top: KD80.2, KSW80.2
matrixr_outer4_func: KD82.2, KSW82.2
matrixr_outer_bottom: KD75.2, KSW75.2
matrixr_outer_func: KD77.2, KSW77.2
matrixr_outer_home: KD33.2, KSW33.2
matrixr_outer_mod: KD32.2, KSW32.2
matrixr_outer_num: KD34.2, KSW34.2
matrixr_outer_top: KD76.2, KSW76.2
matrixr_pinky_bottom: KD73.2, KSW73.2
matrixr_pinky_home: KD30.2, KSW30.2
matrixr_pinky_mod: KD29.2, KSW29.2
matrixr_pinky_num: KD31.2, KSW31.2
matrixr_pinky_top: KD74.2, KSW74.2
matrixr_ring_bottom: KD70.2, KSW70.2
matrixr_ring_func: KD72.2, KSW72.2
matrixr_ring_home: KD27.2, KSW27.2
matrixr_ring_mod: KD26.2, KSW26.2
matrixr_ring_num: KD28.2, KSW28.2
matrixr_ring_top: KD71.2, KSW71.2
mux0: DIP1.1, DIP2.1, MCU1.20
mux1: DIP1.2, DIP2.2, MCU1.19
mux2: DIP1.3, DIP2.3, MCU1.18
mux3: DIP1.5, DIP2.6, MCU1.17
pages_left_bottom: KD40.2, KSW40.2
pages_left_top: KD85.2, KSW85.2
pages_right_bottom: KD41.2, KSW41.2
pages_right_top: KD86.2, KSW86.2
row0: D1.1, DIP1.7, KD46.1, KD51.1, KD54.1, KD57.1, KD60.1, KD63.1, KD66.1, KD69.1, KD72.1, KD77.1, KD79.1, KD81.1, KD87.1, KD88.1
row1: DIP1.9, KD3.1, KD6.1, KD9.1, KD12.1, KD14.1, KD17.1, KD20.1, KD22.1, KD25.1, KD28.1, KD31.1, KD34.1, KD36.1, KD37.1, KD42.1, KD43.1
row2: KD41.1, KD45.1, KD48.1, KD50.1, KD53.1, KD56.1, KD59.1, KD62.1, KD65.1, KD68.1, KD71.1, KD74.1, KD76.1, KD78.1, KD80.1, KD86.1, MCU1.7
row3: KD2.1, KD5.1, KD8.1, KD11.1, KD13.1, KD16.1, KD19.1, KD21.1, KD24.1, KD27.1, KD30.1, KD33.1, KD35.1, KD40.1, KD82.1, KD85.1, MCU1.8
row4: KD39.1, KD44.1, KD47.1, KD49.1, KD52.1, KD55.1, KD58.1, KD61.1, KD64.1, KD67.1, KD70.1, KD73.1, KD75.1, KD84.1, MCU1.9
row5: D2.1, KD1.1, KD4.1, KD7.1, KD10.1, KD15.1, KD18.1, KD23.1, KD26.1, KD29.1, KD32.1, KD38.1, KD83.1, MCU1.10
special_left_bottom: KD42.2, KSW42.2
special_left_top: KD87.2, KSW87.2
special_right_bottom: KD43.2, KSW43.2
special_right_top: KD88.2, KSW88.2

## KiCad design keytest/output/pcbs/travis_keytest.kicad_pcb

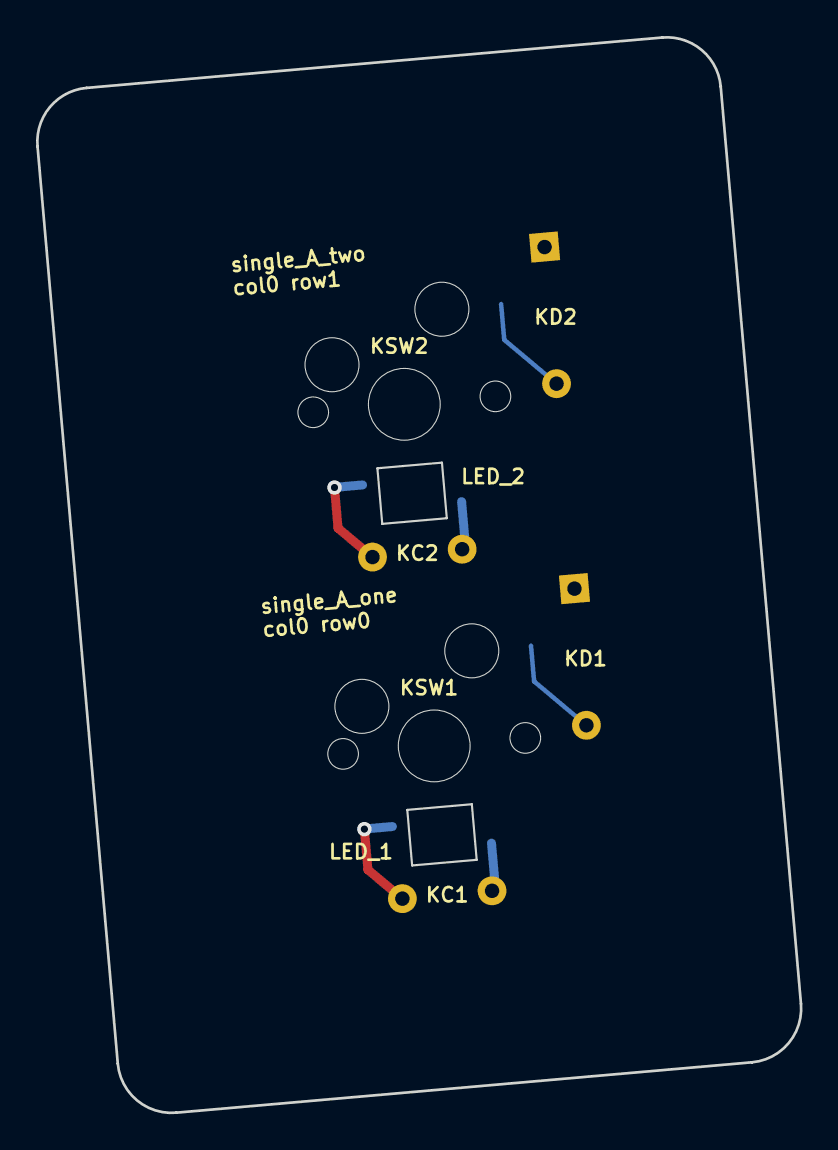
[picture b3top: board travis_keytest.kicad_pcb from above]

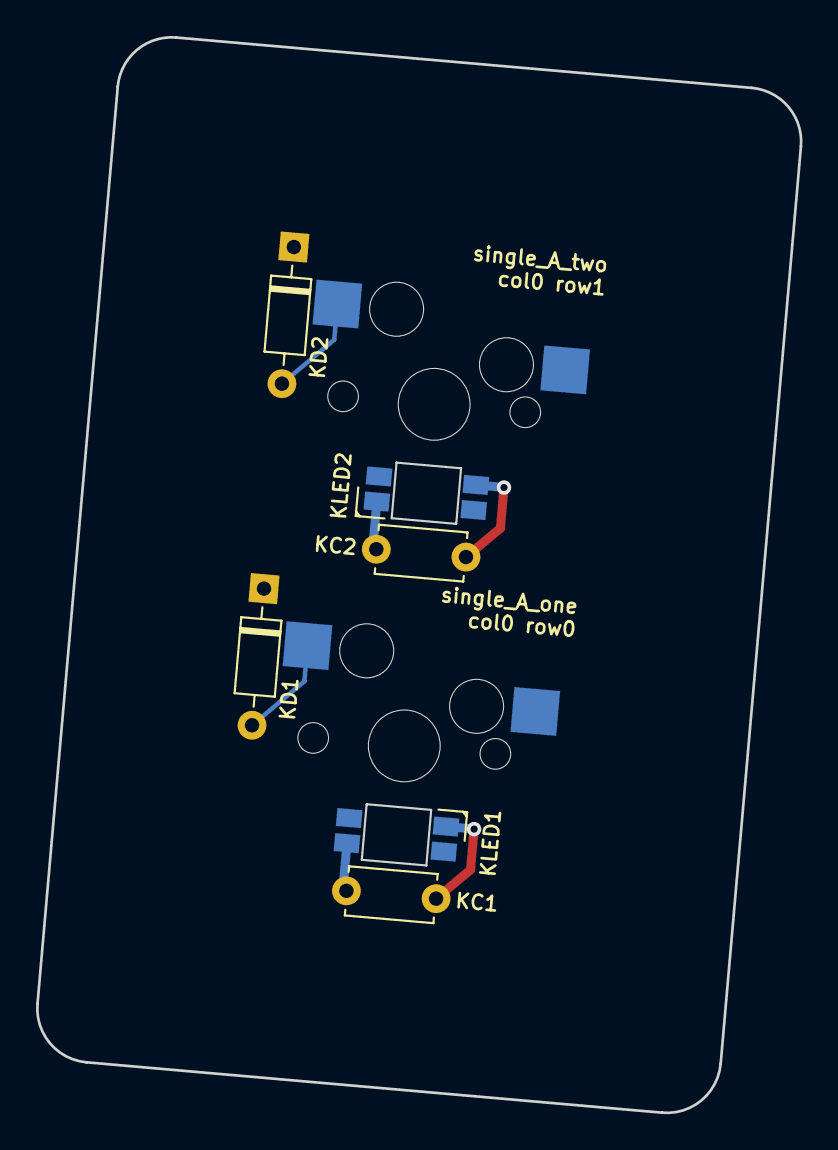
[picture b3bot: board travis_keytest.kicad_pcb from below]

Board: 2 copper layers, 42.4 x 59.7 mm, 8 parts (6 on the bottom side), 6 nets.

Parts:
KC1, KC2: 104; C_Disc_D4.7mm_W2.5mm_P5.00mm
KD1, KD2: 1N4148; Diode_DO-35
KLED1, KLED2: SK6812mini-e; led_SK6812mini-e (per-key single-side)
KSW1, KSW2: Kailh MX Switch Sockets; MX

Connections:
GND: KC1.2, KC2.2, KLED1.3, KLED2.3
LED_2: KLED1.2, KLED2.4
RAW: KC1.1, KC2.1, KLED1.1, KLED2.1
col0: KSW1.1, KSW2.1
single_A_one: KD1.2, KSW1.2
single_A_two: KD2.2, KSW2.2

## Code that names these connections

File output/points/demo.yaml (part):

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                origin:
                    - 0
                    - 0
            matrixl_pinky_mod:
                paths:
                    top:
                        type: line
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                origin:
                    - 0
                    - 0
            matrixl_pinky_bottom:
                paths:
                    top:
                        type: line
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                origin:
                    - 0
                    - 0
            matrixl_pinky_home:
                paths:
                    top:
                        type: line
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                origin:
                    - 0
                    - 0
            matrixl_pinky_top:
                paths:
                    top:
                        type: line
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                origin:
                    - 0
                    - 0
            matrixl_pinky_num:
                paths:
                    top:
                        type: line
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                origin:
                    - 0
                    - 0
            matrixr_pinky_mod:
                paths:
                    top:
                        type: line
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                origin:
                    - 0
                    - 0
            matrixr_pinky_bottom:
                paths:
                    top:
                        type: line
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                origin:
                    - 0
                    - 0
            matrixr_pinky_home:
                paths:
                    top:
                        type: line
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                origin:
                    - 0
                    - 0
            matrixr_pinky_top:
                paths:
                    top:
                        type: line
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                origin:
                    - 0
                    - 0
            matrixr_pinky_num:
                paths:
                    top:
                        type: line
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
